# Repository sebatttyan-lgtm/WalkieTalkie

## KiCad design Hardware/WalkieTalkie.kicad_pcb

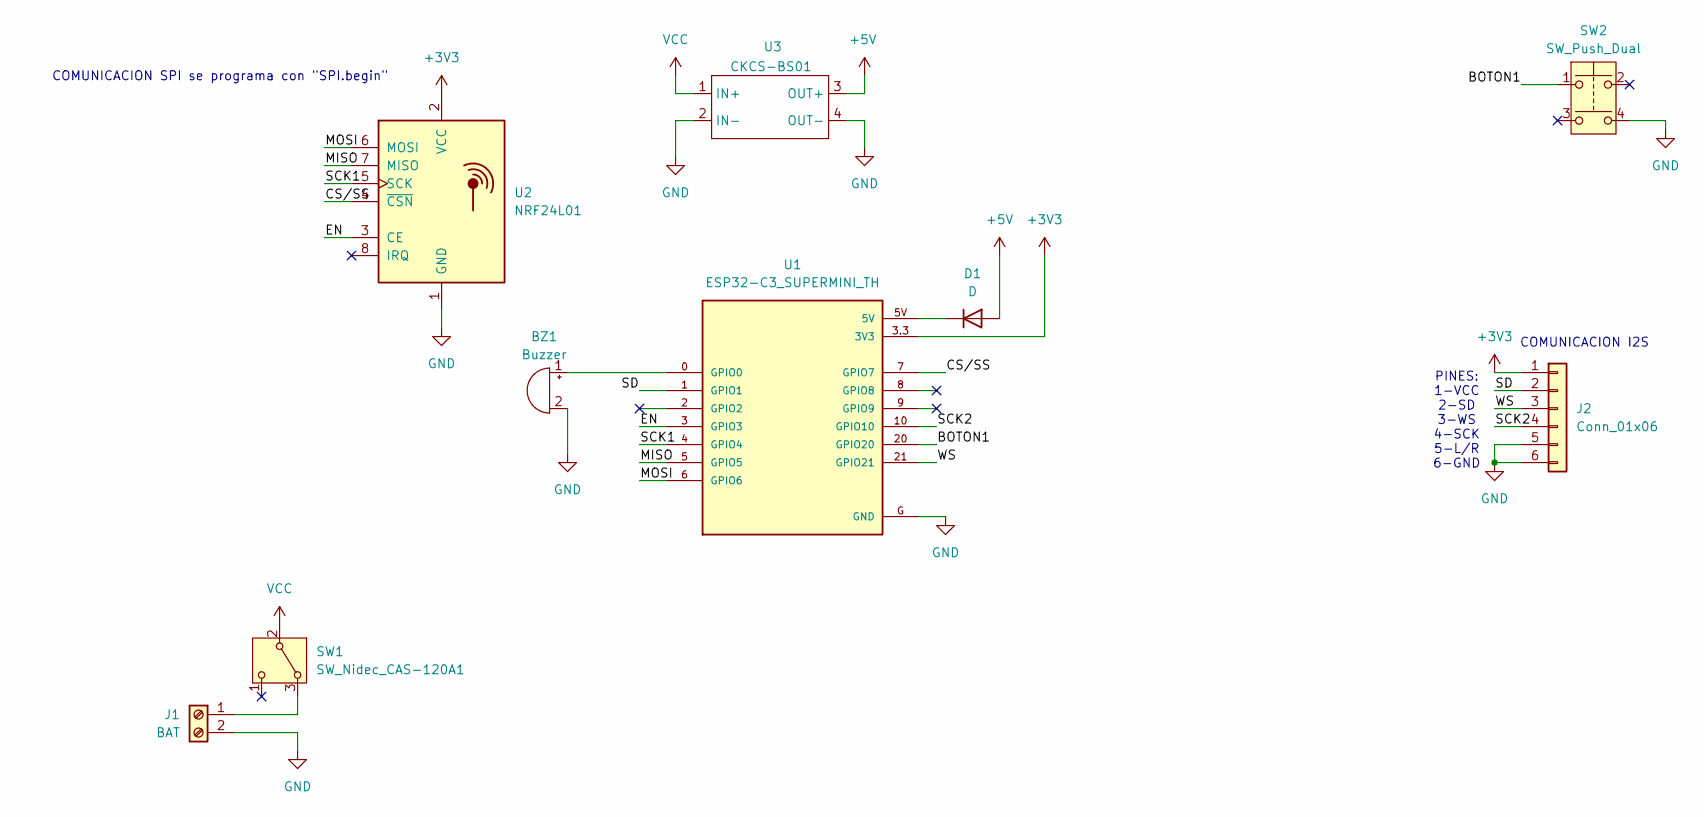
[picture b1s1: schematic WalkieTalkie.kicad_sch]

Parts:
BZ1: Buzzer; Pin_strip_2
D1: D; D_SMA
J1: BAT; TerminalBlock_Phoenix_MKDS-1,5-2-5.08_1x02_P5.08mm_Horizont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
J2: Conn_01x06; PinSocket_1x06_P2.54mm_Vertical
SW1: SW_Nidec_CAS-120A1; PinHeader_1x03_P2.54mm_Vertical
SW2: SW_Push_Dual; SW_PUSH_6mm_H5mm
U1: ESP32-C3_SUPERMINI_TH; MODULE_ESP32-C3_SUPERMINI
U2: NRF24L01; nRF24L01_Breakout
U3: CKCS-BS01; CKCSBS01

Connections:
+3V3: J2.1, U1.3.3 (3V3), U2.2 (VCC)
+5V: D1.2 (A), U3.3 (OUT+)
/CS/SS: U1.7 (GPIO7), U2.4 (~CSN)
/EN: U1.3 (GPIO3), U2.3 (CE)
/MISO: U1.5 (GPIO5), U2.7 (MISO)
/MOSI: U1.6 (GPIO6), U2.6 (MOSI)
/SCK1: U1.4 (GPIO4), U2.5 (SCK)
/SCK2: J2.4, U1.10 (GPIO10)
/SD: J2.2, U1.1 (GPIO1)
/WS: J2.3, U1.21 (GPIO21)
GND: BZ1.2 (-), J1.2, J2.5, J2.6, SW2.4, U1.G (GND), U2.1 (GND), U3.2 (IN-), U3.4 (OUT-)
unnamed: BZ1.1 (+), U1.0 (GPIO0)
unnamed: D1.1 (K), U1.5V
unnamed: J1.1, SW1.3 (A)
unnamed: SW2.1, U1.20 (GPIO20)
VCC: SW1.2 (B), U3.1 (IN+)

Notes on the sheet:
COMUNICACION SPI se programa con "SPI.begin"
PINES: 1-VCC 2-SD 3-WS 4-SCK 5-L/R 6-GND
COMUNICACION I2S

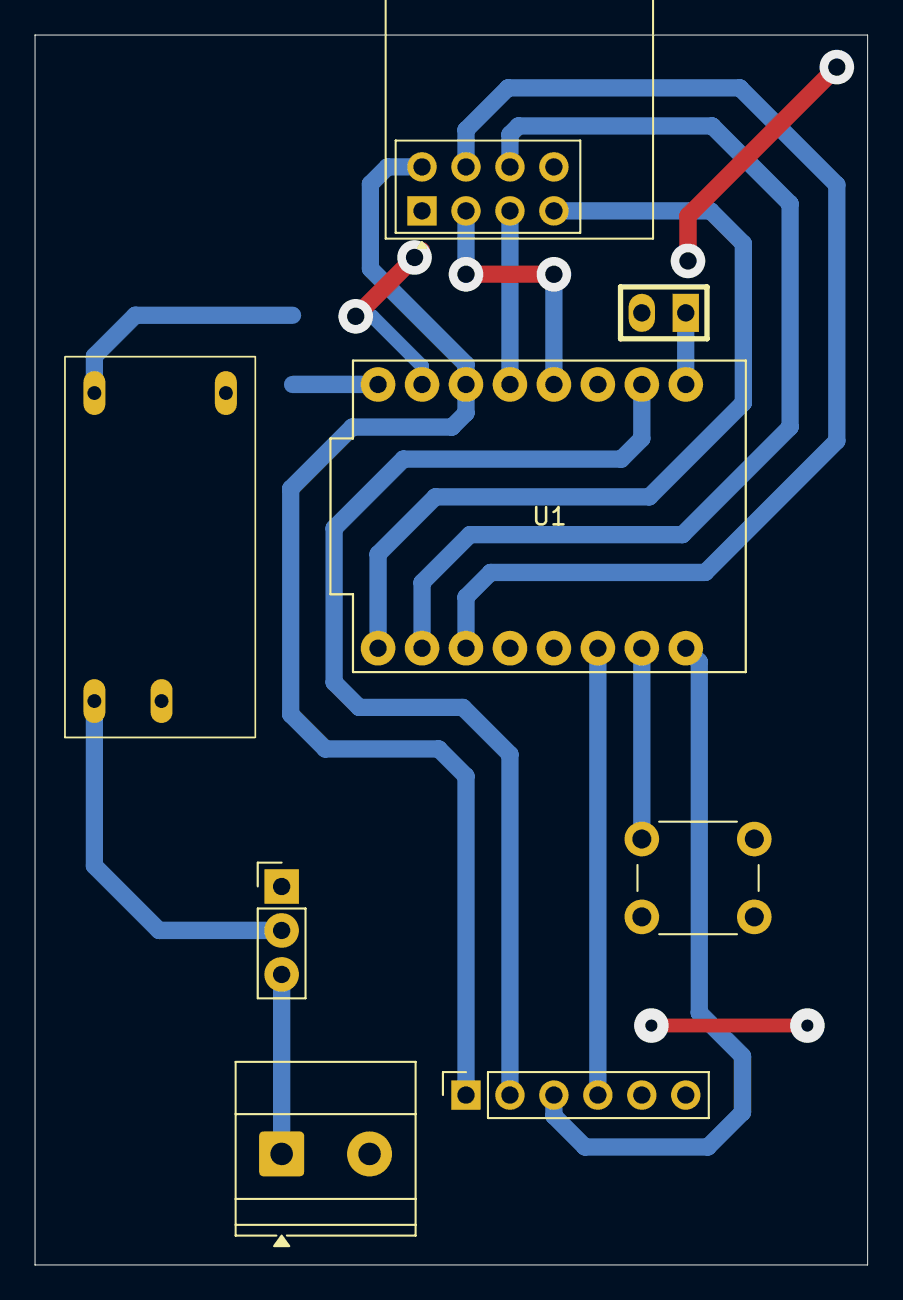
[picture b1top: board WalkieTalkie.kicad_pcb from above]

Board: 2 copper layers, 48.1 x 71.1 mm, 9 parts (1 on the bottom side), 16 nets.
